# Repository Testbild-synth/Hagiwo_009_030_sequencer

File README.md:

# HAGIWO 6 Channel Sequencer / Euclidean Rhythm Sequencer

This project is a through hole PCB version the HAGIWO 009 [six channel gate sequencer](https://www.youtube.com/watch?v=YszdC8YdFl0&t=29s) and 030 [euclidean rythm sequencer](https://www.youtube.com/watch?v=lkoBfiq6KPY) eurorack synth modules. the modules run on an Arduino Nano and uses a [0.96 inch Oled I2C Display](https://www.ebay.de/itm/255303518853). The exact brand is not important, just make sure it is 128/64 pixels and has an SSD1306 driver.
Also, pinout should match the one specified on the PCB:
I saw that there are some modules that have VCC-GND-SCL-SDA, but we need GND-VCC-SCL-SDA

Since both modules use the same hardware, I made it so that the panel pcb is flippable to reflect both functions.

## Status: Don't build this right now, new revision is coming soon!

## PCB and Hardware

You can find the schematic and BOM in the root folder.
For the PCBs, the module has one circuit PCB and one panel PCB. 
You can order them on any common PCB manufacturing service, I used [JLCPCB](https://jlcpcb.com/).
Standard settings should be fine, but if you have exposed copper on the panel you should go with a lead free surface finish (ENIG/Leadfree HASL).

If the panel sizes are not recognized correctly (may happen with my export sometimes) just put 128.5x30.

Use the panel_pcb.zip gerbers if you want a panel with exposed solder mask (so silver letters for title) but then make sure to choose a lead free finish cause health reasons.
If you don't want that, use the "panel_no_silver.zip" version.

The panel PCB is switchable to reflect the function depending on the firmware you want to use.    

## Assembly Instructions

The PCB is relatively simple to build, all the components are through-hole soldering.
It is easiest to start first with the resistors and capacitors, then the headers, and then the jacks at the end.    

The only thing that is a bit tricky is the screen, since depending on your components it can stand out on the top. 
To prevent this, you can try soldering the display directly on the PCB.    

Another optional but good idea is glueing the screen to the panel first before mounting to ensure it is positioned directly behind the cutout.
Downside to glueing is obviously not being able to flip the panel when flashing the firmware so only do it if you build two or are sure you dont need the other side of the panel.

## Arduino Code and Testing

There are three Arduino files included in this project:
- The project file for the six channel drum sequencer (six_channel_sequencer.ino)
- The project file for the euclidean sequencer        (euclid_sequencer.ino)
- A file for testing in/outputs to make sure you soldered everything correctly (test_circuit.ino). This file prints to the serial to test inputs and sets the digital outputs.

You need the [Adafruit_SSD1306](https://www.arduino.cc/reference/en/libraries/adafruit-ssd1306/) and [encoder](https://www.arduino.cc/reference/en/libraries/encoder/) libraries.
I also changed it such that is uses FastGPIO instead of DigitalRead (to recude latency, which was probably not a concern in the first place but I do it in all my arduino projects). See the [FastGPIO](https://github.com/pololu/fastgpio-arduino) repo.

One important change from HAGIWO's code is the introduction of the parameter ENCODER_COUNT_PER_ROTATION. 
Rotation encoders come in different versions, some have one click per rotation, some have two, others even have four. If you see multiple messages during a single turn while running the test_circuit file, set this parameter higher in all files before uploading.

For the six channel sequencer, there are preprogrammed pattern banks you can change (bnk1_ptn, bnk2_ptn, etc.). The patterns are in hexadecimal and represent 16 binary numbers. So for example if the number says 0x8888, this means 1000100010001000, meaning a four on the floor pattern. Use a [hex to binary converter](https://www.rapidtables.com/convert/number/hex-to-binary.html) to help you convert it.

HAGIWO's version only updates the screen when the clock comes in, but I think this makes for a bad user experience so I changed it to update when you turn the encoder as well. 

## TODO:
- Maybe add more rhythm patterns to 6 channel sequencer (taking suggestions here if people want to help me with the work)

## Successful builds

By Felix W.

By Elija

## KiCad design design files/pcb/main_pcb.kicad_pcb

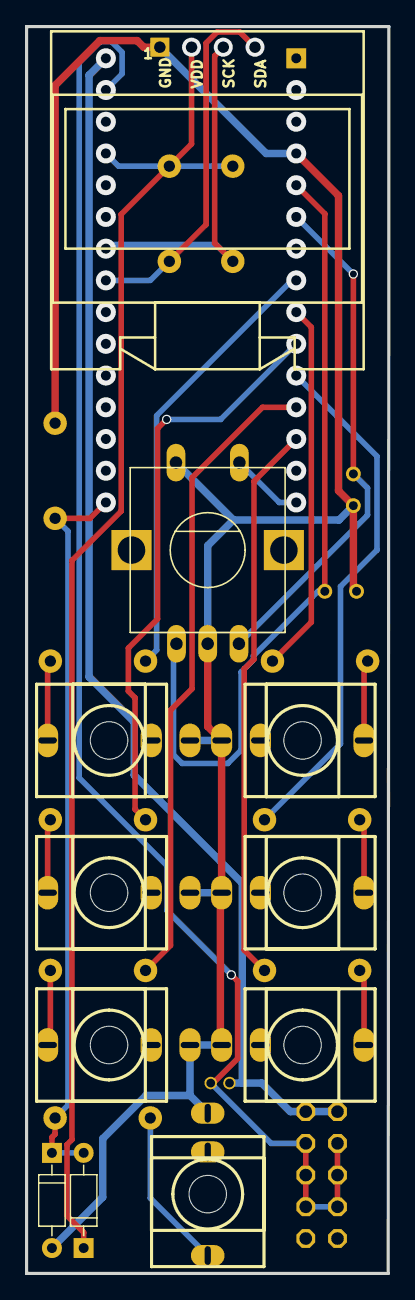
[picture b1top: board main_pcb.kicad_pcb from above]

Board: 2 copper layers, 29.0 x 99.8 mm, 24 parts (0 on the bottom side), 14 nets.

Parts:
1: ALPS_ENCODER+PUSHSWITCHNORMAL; ENCODER+SWITCH
C1, C2: 10n; RAD-0.1
C3: 10u; CAP-D4.0×F1.5
D1, D2: BAT43; D_DO-35_SOD27_P7.62MM_HORIZONTAL
EP1: EURORACK_POWERHEADER_V2; EURORACK_POWER_V2
J1: O1; THONKICONN_1
J2: O5; THONKICONN_1
J3: O2; THONKICONN_1
J4: O6; THONKICONN_1
J5: O3; THONKICONN_1
J6: O4; THONKICONN_1
J7: CLK; THONKICONN_1
R1, R2, R3, R4, R5, R6, R9: 2.2k; R_AXIAL-0.3
R7, R8: 3k3; R_AXIAL-0.3
R10: 100k; R_AXIAL-0.3

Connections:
12V: C3.1, EP1.12
ARD_5: D1.1, R7.1, R8.1
C1_2: 1.B, C1.2
C2_1: 1.A, C2.1
EP1_GND0: C3.2, EP1.GND0, EP1.GND1, EP1.GND2, EP1.GND3, EP1.GND4, EP1.GND5
GND: 1.C, 1.D, C1.1, C2.2, D2.2, J1.1, J2.1, J3.1, J4.1, J5.1, J6.1, J7.1, R10.2
R1_2: J1.3, R1.2
R2_2: J2.3, R2.2
R3_2: J3.3, R3.2
R4_2: J4.3, R4.2
R5_2: J5.3, R5.2
R6_2: J6.3, R6.2
R9_2: J7.3, R9.2
R10_1: D1.2, D2.1, R9.1, R10.1

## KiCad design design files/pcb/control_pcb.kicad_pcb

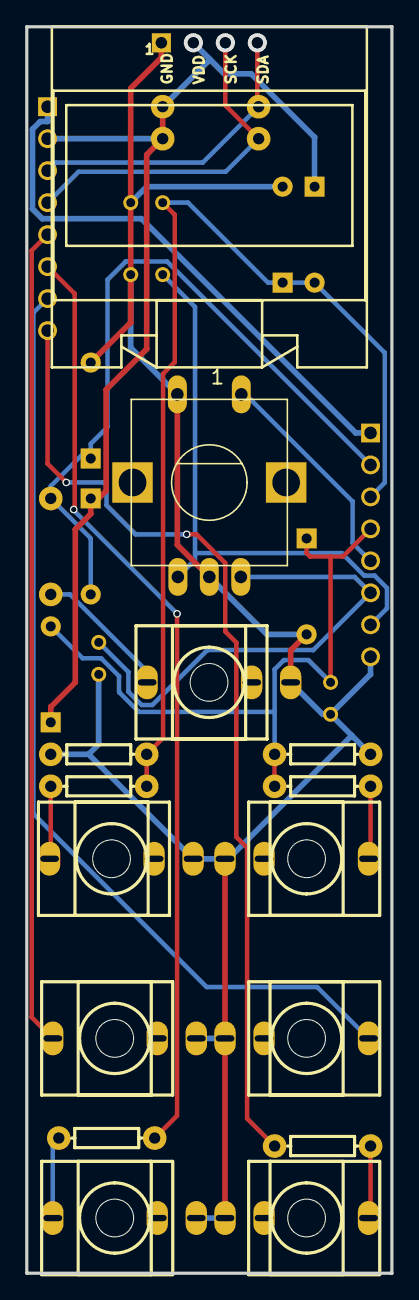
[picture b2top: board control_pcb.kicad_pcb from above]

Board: 2 copper layers, 29.0 x 99.0 mm, 29 parts (0 on the bottom side), 20 nets.

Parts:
1: ALPS_ENCODER+PUSHSWITCHNORMAL; ENCODER+SWITCH
C7, C8, C9, C10: 10n; RAD-0.1
D1, D2, D3, D4, D5, D6: BAT43; D_DO-35_SOD27_P7.62MM_HORIZONTAL
H1, H2: Header-Male-2.54_1x8; HDR-TH_8P-P2.54-V-M
J1: O4; THONKICONN_1
J2: IN3; THONKICONN_1
J3: O1; THONKICONN_1
J4: IN1; THONKICONN_1
J5: IN2; THONKICONN_1
J6: O2; THONKICONN_1
J7: O3; THONKICONN_1
R13, R20: 470; R_AXIAL-0.3
R14, R19: 220k; R_AXIAL-0.3
R15, R21: 330k; R_AXIAL-0.3
R16, R17: 3k3; R_AXIAL-0.3
R18: 33k; R_AXIAL-0.3

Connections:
5V: H1.1, H2.1
ARD_3: D1.1, D3.1, D4.1, H2.2, R16.1, R17.1
ENC_1: 1.B, C8.2, H1.6
ENC_2: 1.A, C9.1, H1.7
ENC_SW: 1.E, H1.5
GND: 1.C, 1.D, C7.1, C8.1, C9.2, C10.1, D2.2, D5.2, D6.2, H1.8, J1.1, J2.1, J3.1, J4.1, J5.1, J6.1, J7.1, R15.2, R21.2
IN_1: D3.2, D5.1, H1.2, R18.1
IN_2: C10.2, D4.2, D6.1, H1.3, R19.1, R21.1
IN_3: C7.2, D1.2, D2.1, H1.4, R14.1, R15.1
J1_3: J1.3, R13.2
J5_3: J5.3, R19.2
J6_3: J6.3, R20.2
O1_CON: H2.5, J3.3
O2_CON: H2.6, R20.1
O3_CON: H2.7, J7.3
O4_CON: H2.8, R13.1
R14_2: J2.3, R14.2
R18_2: J4.3, R18.2
SCL: H2.4, R17.2
SDA: H2.3, R16.2

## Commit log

2022-01-31 added max for display frequency to allow higher bpm
2022-01-31 Add files via upload
    changed digitalReadFast to FastGPIO
2022-02-02 now with panel w/o silver
2022-02-03 consistent folder structure and uploaded kicad files
2022-02-07 uploaded correct design files
2022-02-17 Update README.md
    added note about lead hasl to readme
2022-10-06 new symmetric pcb and panel
2022-10-06 new image
2022-10-06 readme with new image updated
2022-11-30 longer gate time
2022-12-04 bigger resistors
